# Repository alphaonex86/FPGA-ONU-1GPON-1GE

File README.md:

# FPGA-ONU

An open PON endpoint in one chip: 1 GPON/EPON ONU port (BOSA, to the ISP OLT), 1 SFP
cage (switch SFP, or EPON/GPON OLT module for the OLT role) and 1 Gigabit
Ethernet port, with the MACs, the Ethernet PHY and a RISC-V CPU integrated.
Developed and proven on an FPGA, the final target is an ASIC that holds everything.

## Goals

- GPON ONU MAC: GTC framing, FEC, AES-128 decryption, PLOAM, OMCI, upstream
  burst mode with DBA. EPON MAC (MPCP, OAM) and the OLT role of both.
- 1000BASE-T Ethernet port, PHY integrated in the target ASIC (FPGA phase: a
  copper SFP in an SFP+ cage on our HSMC card for the DE25-Standard; its other
  cage takes an OLT module or a normal SFP).
- SFP cage autodetects the module (EEPROM): 1000BASE-X, EPON OLT or GPON OLT.
- BOSA on board; all optics control (burst, APC, LOS, DDM) in the FPGA/ASIC
  logic; outside only analog: discrete RF transistors, a small ADC/DAC, the APD
  bias boost and passives (FPGA phase: an SY88236L BOSA driver on our HSMC
  card, straight to the DE25-Standard GTS transceivers).
- 32-bit RISC-V CPU (VexiiRiscv, rv32imac, no SIMD, no FPU), high energy
  efficiency, power management (clock gating, sleep states, DVFS); MMU (Sv32)
  so it runs Linux.
- Hardware acceleration (line rate, CPU off the data path): GPON, switching,
  VLAN, PPPoE, IPv4 and IPv6 routing, NAT.
- OpenWrt support: upstream-able riscv32 target, drivers for the GPON MAC and GE port.
- Firmware in an external, socketed, user-programmable flash.
- Behaves on the wire exactly like the stock ONU of each brand the OLT expects
  (ZTE, Huawei, ...): no unknown or unanswered message, no drop out of O5; the
  OLT side likewise mimics the stock OLT.
- ONU and OLT at once, each independent on its own segment; through software,
  the exchanges can be dumped and cloned into per-vendor profiles for everyone.
- Vendor-neutral RTL: vendor primitives only in thin wrappers, so the same tree
  goes from FPGA to ASIC.

## Layout

- `common/`: board-neutral parts: RTL and tests (`hw/`), KiCad generator and
  shared parts library (`pcb/gen`, `pcb/lib`).
- `agilex5/`: common to the Agilex 5 boards (Quartus benches, GTS lane variants).
- `de25-standard/`: Terasic DE25-Standard, our HSMC card (`pcb/hsmc`: two SFP+
  cages and the ONU BOSA; placed and routed, DRC/ERC clean, not yet ordered).
- `de25-nano/`: Terasic DE25-Nano, ECP5 SerDes bridge boards (alternative).

## Status

GPON OLT MAC in simulation (SpinalHDL): GTC downstream framer and deframer,
upstream burst receiver, ONU activation (serial number, ONU-ID, ranging, EqD)
with status-reporting DBA (DBRu), checked against G.984.3 vectors and Scala ONU models; the
OLT MAC top (311.04 / 155.52 MHz domains, CPU registers over APB with a
generated C header) meets timing on the DE25-Standard FPGA.
GPON ONU MAC in simulation: activation (O1-O7, TO1/TO2) with the fixed PLOAM set
in hardware (Acknowledge, Password, Alloc-ID and OMCI Port-ID), every other
PLOAM to the CPU, upstream burst framer timed to the bit from the downstream
frame (35 us response); checked in closed loop against our OLT MAC over a
simulated fibre (ranging, DBA, fibre cut and POPUP, Disable_Serial_Number),
and against the PLOAM sequences of real OLTs (ZTE as recorded by stock ONUs,
Broadcom Maple): every copy answered like the stock ONU, EqD drift updates to
the bit, deactivation churn; meets timing on the DE25-Standard FPGA. Like those
OLTs, our OLT sends each of its PLOAMs 3 times. OMCI over GEM both ways:
downstream fragments of the OMCI Port-ID to the CPU, CPU packets upstream in
the default allocation (OMCC), fragmented to the grant, and data GEM at the
same time in up to 4 data T-CONTs, each stream continuing its packet in its
next allocation. DBRu reports of the real backlog (reporting blocks rounded up,
G.984.3 Table 8-1 code, mode 0 and 1). Downstream AES-128
counter-mode decryption of the encrypted Port-IDs with the key switch at the
OLT's superframe, and downstream FEC: RS(255,239) decoding, up to 8 byte errors
corrected per codeword, with the counters of the OMCI FEC PM; checked against
the G.984.3 golden vectors (A.2.2, A.2.3 with FEC, A.3). The OLT sends
downstream FEC when enabled (CTRL register), every codeword's parity checked
against the model and decoded by our ONU in the closed loop. Upstream FEC in
the ONU when the OLT asks for it (Use_FEC): parity per codeword with the shorter
last one, the content sized to the data bytes, checked by a Scala OLT model; our
OLT does not ask for it (like Maple's default).
Ethernet port in simulation: comma alignment and 8b/10b on the raw 10-bit lane,
taxi's 1000BASE-X/SGMII PCS (autonegotiation) and 1G MAC (`common/hw/ext/taxi`,
submodule: `git submodule update --init`), two ports back to back; on the board
its own lane, SFP cage pins and HPS frame queues (`eth_board_regs.h`), checked
from the CPU registers to the looped-back lane.
L2 bridge GEM <-> Ethernet (`common/hw/spinal/pon/GemEthBridge.scala`,
`bridge_regs.h`): per Port-ID action towards Ethernet (drop, CPU, Ethernet;
whole frames with a good FCS), the outer VLAN ID or the untagged default picks
the Port-ID towards the PON, directly or by PCP (802.1p mapper), and the
Port-ID its T-CONT queue (4 on the ONU, each dropping when full without
blocking the others); VLAN treatments each way (G.988 ME 171 subset: push,
pop, translate, PCP set or kept; `VlanRewrite.scala`), the FCS computed after
the rewrite; store-and-forward queues across the four clocks, drops counted.
Flow offload in the bridge, each way (`FlowClassifier.scala`, mtk_ppe model):
frame parser (0-2 VLAN tags, PPPoE session, IPv4/IPv6 TCP/UDP), flow caches
keyed by the 5-tuple, outer VID and PPPoE session (2-way hash in block RAM,
written by the CPU, a hit bit per flow for the driver's stats: IPv4 2K flows
(1K on the board), IPv6 512, routed only, per direction), 64 egress entries (next hop and own MAC, PPPoE
session, VLAN treatment, Port-ID and queue); a hit is rewritten on its way out
(`FlowRewrite.scala`: MACs, PPPoE add/strip, NAPT, TTL or hop limit,
incremental IP and TCP/UDP checksums), a miss follows the L2 rules or, in flows mode (router: per
Port-ID or VLAN entry), goes to the CPU; on each board side the bridge's LAN and
WAN frame queues carry the misses to the CPU and the CPU's own frames out; control frames (ARP, PPPoE
discovery and LCP, DHCP, ICMPv6, IGMP, EAPOL, LLDP, slow protocols) get their own queues and interrupts
behind a token bucket per side, so a miss flood cannot delay them. On the board the Ethernet port goes to the CPU queues or to the
OLT or the ONU bridge (`eth_board_regs.h` BRIDGE); a frame from the lane reaches
the OLT MAC's downstream GEM, or the ONU MAC's upstream data stream, in
simulation; in the closed OLT <-> ONU loop, Ethernet frames cross both bridges
end to end each way, upstream in two T-CONTs granted by our OLT's DBA.
EPON MAC in simulation (`common/hw/spinal/pon/epon/`): clause 36 PCS (8b/10b,
comma sync at any bit slip) with the clause 65 LLID preamble and its CRC-8;
ONU MPCP (discovery with a random offset in the window, REGISTER_REQ/ACK,
timestamp sync and drift, GATE grants timed to the TQ with laser on/off and
sync time, REPORT, deregistration) and OLT MPCP (discovery windows, LLID
allocation, RTT per ONU, IPACT grants from the REPORTs within min/max, CPU and
timeout deregistration, the optics' receiver reset before each burst), checked
together over a simulated splitter with two
ONUs at different distances: no upstream collision, data per LLID each way.
Both MAC tops (`EponOnu.scala`, `EponOlt.scala`) run from their CPU registers
(`epon_onu_regs.h`, `epon_olt_regs.h`: configuration, registration state and
LLID, OLT events, frame counters, interrupts), checked through them alone;
on the DE25-Standard FPGA at 125 MHz: ONU 1.3K ALMs (211 MHz), OLT 2.5K ALMs
(141 MHz). With the same Ethernet bridges as GPON (`EponGem.scala`: the LLID is
the Port-ID, Port-ID 0xFFF the broadcast LLID; the ONU's REPORT from its queues),
Ethernet frames cross OLT port -> ONU port and back in simulation.
HSMC card GTS lanes (two SFP cages, ONU, burst enable) fit in Quartus at their
line rates from their refclk pins (`agilex5/gts/fit.sh`). One GTS dynamic
reconfiguration controller switches cage 0 and the ONU each on its own at run time
between GPON and 1.25 Gb/s, each profile on its own refclk: the cage 0 lane (GPON
OLT, or EPON OLT, 1000BASE-X or SGMII module) and the ONU BOSA lane with its
burst enable lane (EPON ONU); four combinations (GPON or 1.25 Gb/s per side), so
switching one side leaves the other running (to check on the board). Cage 0 with a normal SFP: the OLT core's own
Ethernet port replaces the EPON OLT MAC on the 1.25 Gb/s profile (`olt_board_regs.h`
ETH, set while the lane is reset; frames to the CPU queues at 0xA00), checked in
simulation through the lane; software picks the mode from the module's EEPROM.
Cage 1 is the Ethernet port's. In the board top the EPON MACs run on those profiles with the same bridges
and CPU queues, their registers on each side's bridge slave (0x800, the DR
controller's at 0x900 on the OLT's); the OLT's received words cross from each
profile's rx clock; the EPON ONU is loop-timed like the GPON one, by its own
VCXO loop on the 156.25 MHz VCXO; checked in simulation in both profiles.
Board top (`agilex5/hw/spinal/pon/PonBoard.scala`), OLT side: OLT MAC on its GTS lane
(2x oversampled upstream), HPS lightweight bridge to the MAC and board registers
(GTS reset/status, SFP cage pins, module I2C; `olt_board_regs.h`, `onu_board_regs.h`) and GEM CPU
queues for OMCI (whole packets downstream, upstream fragments with descriptors;
`gem_queues.h`). ONU side: ONU MAC on the BOSA data and burst enable lanes, its
clock kept on the recovered downstream clock by a VCXO loop (DDMTD phase
detector on a helper PLL, 6.7 ps steps, PI, sigma-delta: 0.03 bit of upstream
phase wander in simulation, the OLT tolerating 4), GEM CPU queues for OMCI,
optics pins with the laser held off until both lanes are up. Sniffer (ONU side, 0x900,
`sniffer_regs.h`; with a passive tap on a stock ONU's fibre, the BOSA receiving the downstream copy and a GPON
OLT module in cage 0 that ONU's bursts): one ONU's PLOAMs, BWmap
entries and GEM fragments (still ciphered) and its descrambled bursts, timestamped, read by the CPU as records;
the laser and cage 0's transmitter are held off while it records, and the module gets its burst reset before each
burst, planned from the captured BWmap; checked in simulation. HPS tool `common/sw/sniffer` (`make test`, `make
CC=aarch64-linux-gnu-gcc`): configures it from the exchange (ONU-ID, Alloc-IDs, OMCI Port-ID, delimiter), learns the
burst reset offset, writes raw records (`-w`, keep dumps out of this repo) and a decoded log, replays a dump (`-r`), waits on its interrupt
through UIO (`-u`, overlay from `de25-standard/ghrd/uio_overlay.sh`) or polls `/dev/mem`;
each burst is split by its matched grants into PLOAMu, DBRu and GEM frames, so the stock ONU's OMCI answers sit next
to the OLT's requests; `-P` writes them as an OMCI profile (whole messages paired by TCI: request, answer).
`common/sw/omci` (portable C, `make test`) loads such a profile and answers a request from it with the request's
TCI and a new trailer (AAL5 CRC-32): the clone path for MEs our ONU lacks.
`common/sw/linux` (GPL): the HPS driver of our ONU on the OpenWrt fork's GPON core (`make KDIR=...`): activation
stays in the FPGA, the core's OMCI responder answers on the OMCI Port-ID through the CPU GEM queues, and the core's
clone fallback answers what its ME model lacks from the binary profile (`common/sw/omci/omci_profile`). Not yet:
the Encryption_Key exchange, OMCI to bridge mapping.
Both sides checked in simulation, fit together on the DE25-Standard with the
HSMC card pins placed, flow engine, EPON OLT and ONU, cage 0's Ethernet port and the sniffer included: 40.5K ALMs (87 %), 308 of 358 M20K, setup slack +0.034 ns
(`agilex5/gts/fit.sh out/pon_board PonBoard`).
With the HPS: `de25-standard/ghrd/` brings Terasic's DE25-Standard reference design (GHRD, not in this
repository: `GHRD=<its folder> agilex5/gts/fit.sh <folder outside the repository> ghrd`) to Quartus 26.1, removes
its JTAG debug masters and shrinks its on-chip RAM to make room, and wires PonBoard in: its three register
windows on the HPS lightweight bridge (+0x100000 OLT, +0x101000 ONU, +0x102000 Ethernet), its 18 interrupts on
f2h_irq1 bits 0-17, its management clock the GHRD's 100 MHz: 42.7K ALMs (91 %), 312 of 358 M20K,
setup slack +0.017 ns. A fit folder holding an earlier fit made Quartus 26.1.1 crash (internal error 22912) or fail where a fresh
one passed, so fit.sh empties its own folder and refuses any other non-empty one. The HPS DDR settings were upgraded by Quartus: to check on the board.

## License

Hardware and RTL are licensed under the CERN Open Hardware Licence v2 -
Strongly Reciprocal ([CERN-OHL-S-2.0](LICENSE)). Exception: `common/sw/linux` (the Linux driver, built with the GPL GPON
core of the OpenWrt fork) is GPL-2.0-or-later.

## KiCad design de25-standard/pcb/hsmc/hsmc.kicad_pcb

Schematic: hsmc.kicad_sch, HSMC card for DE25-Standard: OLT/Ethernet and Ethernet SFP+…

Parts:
C1, C2, C7, C8, C11, C12, C15, C16, C18, C25, C27, C30, C32, C35, C36, C37, C38, C39, C40, C41, C42, C45, C46, C47, C48, C49, C51, C60, C61, C63, C65, C66: 100n; C_0402_1005Metric
C3, C4, C17, C26, C28, C31, C33, C43, C44, C50, C52: 10u; C_0603_1608Metric
C5, C6, C22, C23, C24, C29, C34: 22u; C_0805_2012Metric
C9, C10, C13, C14: 1u; C_0402_1005Metric
C19, C20: 10u; C_0805_2012Metric; MPN 10 uF 25 V X5R 0805
C21: 100n; C_0603_1608Metric; MPN 100 nF 25 V
C53, C54: 100n; C_0603_1608Metric; MPN 100 V X7R
C55: 220p; C_0603_1608Metric; MPN 100 V X7R
C56: 47n; C_0402_1005Metric
C57: 2.2u; C_0603_1608Metric
C58, C59: 10p; C_0402_1005Metric
C62: 100n; C_0603_1608Metric; MPN 100 nF 50 V X7R 0603
C64: 47p; C_0402_1005Metric
D1: BAT46WJ; D_SOD-323F; MPN BAT46WJ (100 V)
FB1, FB2, FB3, FB4: 120R@100MHz; L_0603_1608Metric; MPN BLM18PG121SN1D
H1, H2: M3; MountingHole_3.2mm_M3
J1: ASP-122952-01; HSMC_ASP-122952-01; MPN Samtec ASP-122952-01
J2: SFP0 cage; Connector_SFP_and_Cage; MPN SFP+ cage (SFF-8432) + 20-pin host conn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
J3: SFP1 cage; Connector_SFP_and_Cage; MPN SFP+ cage (SFF-8432) + 20-pin host conn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
L1: 2.2u; L_Cenker_CKCS4020; MPN 2.2 uH, Isat >= 4 A, 4020
L2, L3, L4, L5: 1u; L_0805_2012Metric; MPN 1 uH >= 1 A, low DCR
L6: 4.7u; L_Cenker_CKCS252012; MPN 4.7 uH, Isat >= 1 A, 2520
R1, R2, R5, R6: 150; R_0402_1005Metric
R3, R4, R7, R8, R10, R32, R34, R45, R51: 10k; R_0402_1005Metric
R9: 33.2k; R_0402_1005Metric
R11, R19: 33; R_0402_1005Metric
R12, R20: 330; R_0402_1005Metric
R13, R14, R15, R16, R17, R18, R21, R22, R23, R24, R25, R26, R27, R28, R52, R53, R57: 4.7k; R_0402_1005Metric
R29: 5.1k; R_0402_1005Metric
R30: 6.2k; R_0402_1005Metric
R31, R46: 20k; R_0402_1005Metric
R33: 12k; R_0402_1005Metric
R35: 5.6k; R_0402_1005Metric
R36: 3.9k; R_0402_1005Metric
R37, R49: 1.5k; R_0402_1005Metric
R38, R43, R56: 1k; R_0402_1005Metric
R39, R41, R48: 10; R_0402_1005Metric
R40: 15; R_0402_1005Metric
R42: 100; R_0402_1005Metric
R44: 300k; R_0603_1608Metric
R47: 33k; R_0402_1005Metric
R50: 3.01k; R_0402_1005Metric
R54: 0; R_0402_1005Metric; not fitted
R55: 15k; R_0402_1005Metric
R58, R59, R60, R61: 20; R_0402_1005Metric
U1: TPS563201DDCR; SOT-23-6; MPN TPS563201DDCR
U2: SY88236LMG; QFN-32-1EP_5x5mm_P0.5mm_EP3.1x3.1mm_ThermalVias; MPN SY88236LMG
U3: SN65LVDT2DBVR; SOT-23-5; MPN SN65LVDT2DBVR
U4: BOSA GPON (X100DG); BOSA_GPON; MPN desoldered from an X100DG; pad order to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
U5: TPS61391RTER; WQFN-16-1EP_3x3mm_P0.5mm_EP1.68x1.68mm_ThermalVias; MPN TPS61391RTER
U6: AD5593RBRUZ; TSSOP-16_4.4x5mm_P0.65mm; MPN AD5593RBRUZ
U7: SN74LVC1G123DCUR; VSSOP-8_2.3x2mm_P0.5mm; MPN SN74LVC1G123DCUR
U8: SN74LVC1G97DBVR; SOT-23-6; MPN SN74LVC1G97DBVR
U9: SN74LVC1G32DBVR; SOT-23-5; MPN SN74LVC1G32DBVR
Y1: SiT3821 156.25 MHz; Oscillator_SMD_SiTime_SiT9121-6Pin_3.2x2.5mm; MPN SiT3821AI-1B2-33NH156.250000
Y2: SiT3821 155.52 MHz; Oscillator_SMD_SiTime_SiT9121-6Pin_3.2x2.5mm; MPN SiT3821AI-1B2-33NE155.520000

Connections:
+3V3: C1.1, C2.1, C3.1, C4.1, C5.1, C6.1, C61.1, C63.1, C65.1, C66.1, FB1.1, FB2.1, FB4.1, J1.45 (3.3V), J1.51 (3.3V), J1.57 (3.3V), J1.63 (3.3V), J1.69 (3.3V), J1.75 (3.3V), J1.81 (3.3V), J1.87 (3.3V), J1.93 (3.3V), J1.99 (3.3V), J1.105 (3.3V), J1.111 (3.3V), J1.117 (3.3V), J1.123 (3.3V), J1.129 (3.3V), J1.135 (3.3V), J1.141 (3.3V), J1.147 (3.3V), J1.153 (3.3V), J1.159 (3.3V), R27.2, R28.2, R51.2, R52.2, R53.2, R55.2, R57.2, U6.3 (V_{DD}), U6.9 (V_{LOGIC}), U7.3 (~CLR), U7.8 (VCC), U8.5 (VCC), U9.5 (VCC)
+3V3_APD: C51.1, C52.1, FB4.2, L6.1, R48.1, U5.10 (VIN), U5.13 (EN)
+3V3_APDA: C57.1, R48.2, U5.14 (AVCC), U5.15 (AVCC)
+3V3_OPT: C39.1, C40.1, C41.1, C42.1, C43.1, C44.1, C45.1, FB2.2, FB3.1, R29.2, R40.2, U2.17 (VCC), U2.20 (VCC), U2.32 (VCC), U3.1 (VCC), U4.T1 (LD_A), U4.T4 (MPD_K)
+3V3_RX: C48.1, C49.1, C50.1, FB3.2, U4.R2 (VCC)
+3V3_SFP: C22.1, C23.1, C24.1, C29.1, C34.1, L1.2, L2.1, L3.1, L4.1, L5.1, R9.1, R13.2, R14.2, R15.2, R16.2, R17.2, R18.2, R21.2, R22.2, R23.2, R24.2, R25.2, R26.2
+3V3_SFP0R: C27.1, C28.1, J2.15 (VccR), L3.2
+3V3_SFP0T: C25.1, C26.1, J2.16 (VccT), L2.2
+3V3_SFP1R: C32.1, C33.1, J3.15 (VccR), L5.2
+3V3_SFP1T: C30.1, C31.1, J3.16 (VccT), L4.2
+3V3_XO: C15.1, C16.1, C17.1, FB1.2, Y1.6 (VDD), Y2.6 (VDD)
+12V: C19.1, C20.1, C21.1, J1.88 (12V), J1.94 (12V), J1.100 (12V), U1.3 (VIN), U1.5 (EN)
APCFAULT_N: U2.25 (~APCFAULT), U6.13 (IO7)
APCSET: R31.1, R32.1, U2.12 (APCSET)
APC_ADJ: R32.2, U6.4 (IO0)
APD_ADJ: R46.2, U6.6 (IO2)
APD_CAP: C56.1, U5.9 (CAP)
APD_FB: R44.2, R45.1, R46.1, U5.12 (FB)
APD_ISHORT: R47.1, U5.11 (ISHORT)
APD_MON: C58.1, R49.1, U5.4 (MON1), U6.11 (IO5)
APD_MON2: C59.1, R50.1, U5.3 (MON2)
BEN_DLY: C64.1, R56.2, U8.1 (IN1)
BEN_IO: J1.120 (LVDS_RXp11), R54.1
BIASMAX: R35.1, U2.14 (BIASMAX)
BIASMON: R37.1, U2.23 (BIASMON), U6.7 (IO3)
BST_SFP: C18.1, U1.6 (VBST)
BURST_CUT: J1.116 (LVDS_RXn10), U8.4 (Y), U9.2
CUT_C: C62.1, U7.6 (Cext)
CUT_Q: U7.5 (Q), U8.6 (IN2)
CUT_RC: C62.2, R55.1, U7.7 (RCext)
DDM_RESET: R51.1, U6.1 (~RESET)
DDM_VREF: C60.1, U6.8 (V_{REF})
FB_SFP: R9.2, R10.1, U1.4 (VFB)
GND: C1.2, C2.2, C3.2, C4.2, C5.2, C6.2, C9.2, C10.2, C13.2, C14.2, C15.2, C16.2, C17.2, C19.2, C20.2, C21.2, C22.2, C23.2, C24.2, C25.2, C26.2, C27.2, C28.2, C29.2, C30.2, C31.2, C32.2, C33.2, C34.2, C39.2, C40.2, C41.2, C42.2, C43.2, C44.2, C45.2, C48.2, C49.2, C50.2, C51.2, C52.2, C53.2, C54.2, C55.2, C56.2, C57.2, C58.2, C59.2, C60.2, C61.2, C63.2, C64.2, C65.2, C66.2, J1.160 (PSNTn), J1.161 (GND), J1.162 (GND), J1.163 (GND), J1.164 (GND), J1.165 (GND), J1.166 (GND), J1.167 (GND), J1.168 (GND), J1.169 (GND), J1.170 (GND), J1.171 (GND), J1.172 (GND), J2.1 (VeeT), J2.10 (VeeR), J2.11 (VeeR), J2.14 (VeeR), J2.17 (VeeT), J2.20 (VeeT), J2.CAGE, J3.1 (VeeT), J3.10 (VeeR), J3.11 (VeeR), J3.14 (VeeR), J3.17 (VeeT), J3.20 (VeeT), J3.CAGE, R1.2, R2.2, R5.2, R6.2, R10.2, R30.2, R31.2, R33.2, R35.2, R36.2, R37.2, R38.2, R45.2, R47.2, R49.2, R50.2, U1.1 (GND), U2.1 (LOS/SD_SEL), U2.5 (GND), U2.8 (GND), U2.16 (GND), U2.24 (GND), U2.29 (GND), U2.33 (EP), U3.2 (GND), U4.R5 (GND), U5.7 (GND), U5.16 (AGND), U5.17 (EP), U6.2 (A0), U6.14 (GND), U7.1 (~A), U7.4 (GND), U8.2 (GND), U8.3 (IN0), U9.3 (GND)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
GTS_REFCLK_AC_N: C8.2, R59.1
GTS_REFCLK_AC_P: C7.2, R58.1
GTS_REFCLK_N: J1.8 (XCVR_RXn6), R59.2
GTS_REFCLK_P: J1.6 (XCVR_RXp6), R58.2
GTS_RXREF_AC_N: C12.2, R61.1
GTS_RXREF_AC_P: C11.2, R60.1
GTS_RXREF_N: J1.4 (XCVR_RXn7), R61.2
GTS_RXREF_P: J1.2 (XCVR_RXp7), R60.2
HV_APD: C55.1, U4.R1 (VAPD), U5.5 (APD)
HV_FILT: C54.1, R42.2, R43.1
HV_MONIN: R43.2, U5.6 (MONIN)
HV_OUT: C53.1, D1.1 (K), R42.1, R44.1
HV_SW: D1.2 (A), L6.2, U5.8 (SW)
LASER_DIS: R27.1, U2.11 (TXDIS), U9.4
LASER_DIS_FPGA: J1.102 (LVDS_RXp8), R57.1, U9.1
LD_BEN: R54.2, R56.1, U2.9 (BEN+), U3.5 (R), U7.2 (B)
LD_BEN_N: R30.1, U2.10 (BEN-)
LD_BIAS: R41.1, U2.21 (BIAS)
LD_K: R39.2, R41.2, U4.T2 (LD_K)
LD_MD: U2.22 (MD), U4.T3 (MPD_A)
LD_MODN: R40.1, U2.18 (MOD-)
LD_MODP: R39.1, U2.19 (MOD+)
LOSLVL: R29.1, U2.2 (LOSLVL)
MODMON: R36.1, U2.15 (MODMON), U6.10 (IO4)
MODSET: R33.1, R34.1, U2.13 (MODSET)
MOD_ADJ: R34.2, U6.5 (IO1)
ONU_BEN_N: J1.31 (XCVR_TXn0), U3.4 (B)
ONU_BEN_P: J1.29 (XCVR_TXp0), U3.3 (A)
ONU_RD_N: C38.1, U2.30 (ROUT-)
ONU_RD_P: C37.1, U2.31 (ROUT+)
ONU_RX_N: C38.2, J1.26 (XCVR_RXp1)
ONU_RX_P: C37.2, J1.28 (XCVR_RXn1)
ONU_SCL: J1.108 (LVDS_RXp9), R52.1, U6.16 (SCL)
ONU_SDA: J1.110 (LVDS_RXn9), R53.1, U6.15 (SDA)
ONU_TD_N: C36.2, U2.6 (DIN+)
ONU_TD_P: C35.2, U2.7 (DIN-)
ONU_TX_N: C36.1, J1.25 (XCVR_TXp1)
ONU_TX_P: C35.1, J1.27 (XCVR_TXn1)
RIN_N: C47.2, U2.28 (RIN-)
RIN_P: C46.2, U2.27 (RIN+)
RSSI: R38.1, U2.26 (RSSI), U6.12 (IO6)
RX_SD: J1.104 (LVDS_RXn8), R28.1, U2.3 (LOS/SD), U2.4 (~JAM)
SFP0_LOS: J1.48 (LVDS_RXp0), J2.8 (RX_LOS), R15.1
SFP0_MOD_ABS: J1.50 (LVDS_RXn0), J2.6 (MOD_ABS), R16.1
SFP0_P7: J2.7 (RS0), R11.2
SFP0_P9: J2.9 (RS1), R12.2
SFP0_RD_N: J1.18 (XCVR_RXp3), J2.12 (RD-)
SFP0_RD_P: J1.20 (XCVR_RXn3), J2.13 (RD+)
SFP0_RS0: J1.60 (LVDS_RXp2), R11.1
SFP0_RS1: J1.62 (LVDS_RXn2), R12.1
SFP0_SCL: J1.54 (LVDS_RXp1), J2.5 (SCL), R17.1
SFP0_SDA: J1.56 (LVDS_RXn1), J2.4 (SDA), R18.1
SFP0_TD_N: J1.19 (XCVR_TXn3), J2.19 (TD-)
SFP0_TD_P: J1.17 (XCVR_TXp3), J2.18 (TD+)
SFP0_TX_DIS: J1.42 (D1), J2.3 (TX_DISABLE), R14.1
SFP0_TX_FAULT: J1.44 (D3), J2.2 (TX_FAULT), R13.1
SFP1_LOS: J1.72 (LVDS_RXp4), J3.8 (RX_LOS), R23.1
SFP1_MOD_ABS: J1.74 (LVDS_RXn4), J3.6 (MOD_ABS), R24.1
SFP1_P7: J3.7 (RS0), R19.2
SFP1_P9: J3.9 (RS1), R20.2
SFP1_RD_N: J1.22 (XCVR_RXp2), J3.12 (RD-)
SFP1_RD_P: J1.24 (XCVR_RXn2), J3.13 (RD+)
SFP1_RS0: J1.84 (LVDS_RXp6), R19.1
SFP1_RS1: J1.86 (LVDS_RXn6), R20.1
SFP1_SCL: J1.78 (LVDS_RXp5), J3.5 (SCL), R25.1
SFP1_SDA: J1.80 (LVDS_RXn5), J3.4 (SDA), R26.1
SFP1_TD_N: J1.23 (XCVR_TXn2), J3.19 (TD-)
SFP1_TD_P: J1.21 (XCVR_TXp2), J3.18 (TD+)
SFP1_TX_DIS: J1.66 (LVDS_RXp3), J3.3 (TX_DISABLE), R22.1
SFP1_TX_FAULT: J1.68 (LVDS_RXn3), J3.2 (TX_FAULT), R21.1
SW_SFP: C18.2, L1.1, U1.2 (SW)
TIA_N: C47.1, U4.R4 (OUT-)
TIA_P: C46.1, U4.R3 (OUT+)
VCXO156_N: C8.1, R2.1, Y1.5 (OUT-)
VCXO156_P: C7.1, R1.1, Y1.4 (OUT+)
VCXO156_PWM: J1.122 (LVDS_RXn11), R3.1
VCXO156_RC: C9.1, R3.2, R4.1
VCXO156_VC: C10.1, R4.2, Y1.1 (VIN)
VCXO_N: C12.1, R6.1, Y2.5 (OUT-)
VCXO_P: C11.1, R5.1, Y2.4 (OUT+)
VCXO_PWM: J1.114 (LVDS_RXp10), R7.1
VCXO_RC: C13.1, R7.2, R8.1
VCXO_VC: C14.1, R8.2, Y2.1 (VIN)

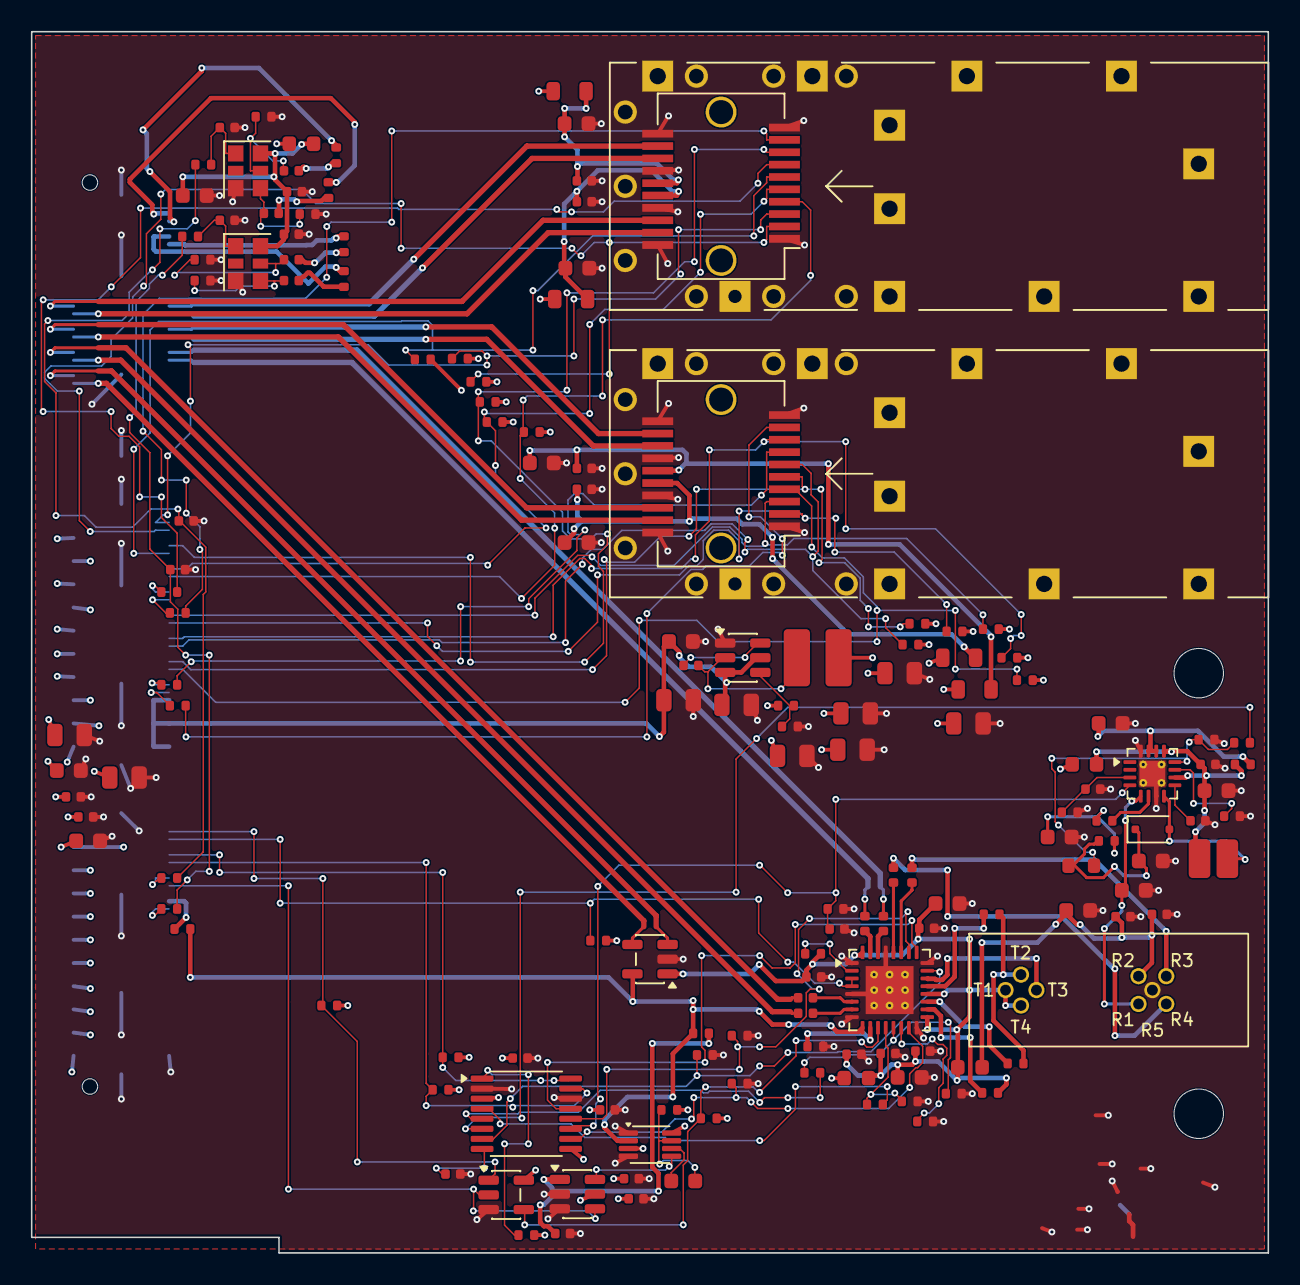
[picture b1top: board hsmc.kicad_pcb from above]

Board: 4 copper layers, 80.0 x 79.0 mm, 154 parts (1 on the bottom side), 117 nets.

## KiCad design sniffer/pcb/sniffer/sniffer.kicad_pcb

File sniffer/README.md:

# GPON sniffer

A passive tap on one ONU's drop fibre: both directions of that ONU's GPON traffic,
filtered to what concerns it, dumped with the direction of every record. Simple and
cheap: one small card on the DE25-Nano 40-pin GPIO. Origin: `../common/sniffer/sniffer-GPON.jpg`.

Versus the FPGA ONU (operator, 2026-11-02): the ONU + OLT proxy of this repo sits in the path
and can intervene in the packets; the sniffer cannot touch anything, it only listens, but it
dumps without complications (no activation, no cloning, the stock ONU keeps its link).

## Decisions (operator, 2026-11-02)

- Customer side, not provider: the OLT is the ISP's, remote and out of our hands. The tap goes
  between the wall fibre outlet and our own ONU; the sniffer must stay invisible to the ISP
  (passive, never emits; our ONU receives about 4 dB less, see Coupler).
- The link: about 5 km of fibre from the ISP; our ONU reports
  -17 to -27 dBm received. -27 dBm is already at a class B+ ONU's sensitivity (-27/-28 dBm),
  so any optical tap that takes light from the downstream can drop our ONU off the PON.
  Range across installations: the sniffer is for homes at -23 dBm or better (Coupler).
- Tap: two 1x2 couplers back to back in our ONU's drop (Coupler below), so the two
  directions arrive on two fibres (no WDM) and the upstream holds our ONU's bursts only,
  at one constant power.
- Optics: two BOSAs, receive only. Downstream: an ONU BOSA RX (X100DG, 1490 nm, APD-TIA).
  Upstream: the OLT BOSA XL-BCB2111-LS-02 RX (1310 nm, 1.25 Gb/s APD-TIA, -32 dBm). Each
  into a SY88349NDL limiting amp. No laser driver is fitted: the sniffer cannot emit into
  the PON, by construction. SFP modules were dropped: no raw GPON ONU module without a MAC
  on AliExpress (only "sticks" with a MAC); raw ones exist at Optcore/FiberMall/PLANET.
- Platform: an ECP5 SerDes card on the DE25-Nano GPIO (the `../de25-nano/pcb` bridge
  plan; the operator owns a DE25-Nano). The ECP5 deserialises; the Agilex runs the existing GTC deframer, FEC, AES
  and the filter; the HPS writes the dump.

## Coupler (operator, 2026-11-02)

Two 1x2 back to back: wall - [common 1x2 #1 50 %] - [90 % 1x2 #2 common] - ONU. The free leg of #1
is the downstream copy, the 10 % leg of #2 the upstream copy (one 1x2 alone taps one direction:
the light entering a leg leaves by the common port). #1 is a 50:50, #2 a 90:10: the
operator has several of each (unbalanced 1x2 for building GPON networks).
- ONU: about 4 dB less (3.5 + 0.5). The -17 to -27 dBm range is across installations, so the
  sniffer fits a home whose ONU reports -23 dBm or better without the tap (it then stays at
  -27 dBm or better, a class B+ ONU's sensitivity).
- Downstream: the sniffer gets the ONU's tapped level + 0.5 dB, at least -26.5 dBm there, above
  the APD's -28 dBm.
- Upstream: the ONU emits +0.5 to +5 dBm, the sniffer sees about -10 to -5.5 dBm, near an APD's
  overload (-8 dBm typical for an OLT receiver): a 5 dB SC attenuator on the upstream tap fibre.

## DE25-Nano: verified (2026-11-02)

- GPIO headers are 3.3 V HVIO: 100 MHz SDR or 200 Mb/s DDR per pin (Altera Agilex 5 GPIO
  architecture brief); the HVIO clock input reaches the I/O PLL up to 156.25 MHz (data sheet).
- So the card sends DDR: DS 2.48832 Gb/s on 16 pins + US 1.24416 Gb/s on 8 pins, 155.52 Mb/s
  per pin (78 % of the limit) on a 77.76 MHz forwarded clock. With CCLK/MOSI/MISO/SN/PROGRAMN
  (slave-SPI configuration from the Agilex) and I2C: 36 of the 40 pins of GPIO_0.
- The Agilex A5EB013 is the DE25-Standard's density (138K LE), where the GTC/FEC/AES already
  meet timing; the HPS has the GbE port and the microSD for the dump.
- The two ECP5 bridge boards in `../de25-nano/pcb` send 155.52 MHz SDR: above the 100 MHz HVIO limit.

## Card (`pcb/sniffer`, generated by `../common/pcb/gen`)

Routed 2026-11-02: KRT, then close_opens on the last 5 nets; KiCad: 0 errors, 0 unconnected.

ECP5 LFE5UM-25F (as the bridge boards), SerDes RX only: CH0 downstream (CDR), CH1 upstream
(lock-to-reference on the 155.52 MHz VCXO, which the ECP5 locks to the downstream like the
ONU board, so each burst needs only a phase pick). Each BOSA: receive can only, into a
SY88349NDL burst-mode limiting amp (SD mode, auto reset, squelch), its own TPS61391 APD bias
(DAC trim from an AD5593R, which also reads both APD currents = optical power at the tap).
Upstream coupling 220 pF (tau 11 ns), downstream 100 nF.

## Filter (downstream; the upstream is already this ONU only)

The ONU is named by its serial number. From the PLOAMs: Assign_ONU-ID (serial ->
ONU-ID), Assign_Alloc-ID, Configure_Port-ID (OMCI); from OMCI: the GEM Port CTPs
(data Port-IDs). Kept: PLOAMs to that ONU-ID or broadcast, the BWmap entries of its
Alloc-IDs, the GEM frames of its Port-IDs.

## RTL (`../common/hw/spinal/pon/sniffer`, test `pon.sniffer.SnifferTest`)

Vendor-neutral SpinalHDL, one line byte per clock per direction; no AES in hardware.
- `SnifferDs` (311.04 MHz): the GTC deframer (FEC included), then the filter: PLOAMs to
  `onuId` or broadcast (all with `allPloams`), BWmap entries and GEM fragments by two
  4096-bit maps (Alloc-ID, Port-ID) the HPS writes. GEM stays ciphered; its record carries
  the crypto-counter, the software decrypts.
- `SnifferUs` (155.52 MHz): delimiter hunt on any bit alignment, descramble from the BIP,
  one record per burst until 8 squelched (zero) line bytes.
- `RecordWriter`: the record stream; a record is kept or dropped whole, a full data FIFO
  cuts its tail (flag bit 7); drop and truncation counters.

Record: `0xA0|kind`, flags, payload length (16 LE), time (64 LE), payload.

| kind | payload | flags |
|------|---------|-------|
| 0 PLOAM | 12 bytes | 0: bad CRC |
| 1 allocation | 7 bytes as on the line | 0: bad CRC |
| 2 GEM fragment | Port-ID 16, PLI 16, counter 48, data | 2..0: PTI, 3: cut |
| 3 upstream burst | BIP, ONU-ID, Ind, allocations | 0: maxBytes reached |

ECP5 (`ecp5/`, `sh sniffer/ecp5/build.sh` -> `out/ecp5/sniffer.bit`, yosys + nextpnr + trellis):
`sniffer_ecp5.v` (DCU, resets, PLL, DDR pins) around `SnifferBridge` (test `pon.sniffer.SnifferBridgeTest`);
`gen.py` writes the DCU parameters and the LPF from the routed board. All in the VCXO's domain
(124.416 MHz, CH0's TX clock): CH1 is read there; the downstream crosses a 16-word FIFO whose
fill is the phase detector of the VCXO loop (PI every 132 us, sigma-delta on VCXO_PWM;
`ecp5/vcxo_loop_model.py`: locked to 0.5 word in 14 s from 10 ppm). Upstream: one sample per
pair, the centre of isolated 1- or 3-sample runs (an edge on a sample reads either bit).
Timing (speed 6): VCXO domain 135.6 MHz for 124.4, out 125 for 77.8, DS 255 for 124.4.

Still to write: the Agilex wrapper (DDR capture, x4 / x2 serialisers, time base, both
streams to the HPS).

## Dump

pcapng, one interface per direction (0 = downstream, 1 = upstream), hardware
timestamps; one packet per record.

## Open

- SY88349NDL stock (LCSC not reachable from here) and its SD level resistor (5.1k start).
- Lead order of the X100DG BOSA's RX can (to measure); XL-BCB2111 order from its drawing.
- XL-BCB2111 connector: SC/UPC in the title, SC/APC on the drawing.
- CH1 between bursts: with the line squelched the DCU sees LOS and its phase detector stops
  (`PDEN_SEL`); the 2x pick needs the DCO to stay on the reference frequency there, to measure.
- DCU bit order: the first received bit taken in D0 (as LiteICLink's 8b10b path); a reversed
  lane would show as a deframer that never syncs.
- VCXO: its pull range must exceed its initial error plus ageing (SiT3821: pick >= +-100 ppm).
- ECP5 in the BOM is the C grade (LFE5UM-25F-6BG381C): the I grade is the industrial one.
- 5 dB attenuator part number; connectors (drop SC/APC, BOSA pigtails per part).

## Docs

`../common/sniffer/`: block diagram (`sniffer-diagram.dot` -> `.svg`/`.png`) and the prompt for a
realistic photo of the finished device (`sniffer-render-prompt.md`, Nano Banana Pro).

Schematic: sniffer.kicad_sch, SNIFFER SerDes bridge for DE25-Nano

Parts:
C1, C3, C6, C9, C24, C25, C30, C48, C49, C50, C51, C54, C57, C60, C63, C65, C71, C80, C87, C96: 10u; C_0603_1608Metric
C2, C4, C5, C7, C8, C10, C11: 22u; C_0805_2012Metric
C12, C13, C66, C67: 1u; C_0402_1005Metric
C14, C15, C16, C17, C18, C19, C20, C21, C22, C23, C26, C27, C28, C29, C31, C32, C33, C34, C35, C36, C37, C38, C39, C40, C41, C42, C43, C44, C45, C46, C47, C52, C53, C55, C56, C58, C59, C61, C62, C64, C68, C69, C70, C72, C73, C74, C75, C76, C77, C78, C79, C83, C84, C85, C86, C95, C104, C105: 100n; C_0402_1005Metric
C81, C82: 220p; C_0402_1005Metric
C88, C89, C97, C98: 100n; C_0603_1608Metric; MPN 100 V X7R
C90, C99: 220p; C_0603_1608Metric; MPN 100 V X7R
C91, C100: 47n; C_0402_1005Metric
C92, C101: 2.2u; C_0603_1608Metric
C93, C94, C102, C103: 10p; C_0402_1005Metric
D1, D2: BAT46WJ; D_SOD-323F; MPN BAT46WJ (100 V)
FB1, FB2, FB3, FB4, FB5, FB6, FB7, FB8, FB9, FB10: 120R@100MHz; L_0603_1608Metric; MPN BLM18PG121SN1D
H1, H2: M3; MountingHole_3.2mm_M3
J1: DE25-Nano GPIO; PinSocket_2x20_P2.54mm_Vertical
J2: JTAG; PinHeader_1x06_P2.54mm_Vertical
L1, L2: 2.2u; L_Cenker_CKCS252012; MPN CKCS252012-2R2M
L3, L4: 4.7u; L_Cenker_CKCS252012; MPN 4.7 uH, Isat >= 1 A, 2520
R1, R3: 100k; R_0402_1005Metric
R2, R4: 120k; R_0402_1005Metric
R5, R6, R7, R8, R9, R12, R13, R14, R20, R24: 4.7k; R_0402_1005Metric
R10, R15, R16, R28, R37, R43, R46: 10k; R_0402_1005Metric
R11, R26, R35: 1k; R_0402_1005Metric
R17, R18, R21, R22: 49.9; R_0402_1005Metric
R19, R23: 5.1k; R_0402_1005Metric
R25, R34: 100; R_0402_1005Metric
R27: 300k; R_0603_1608Metric
R29, R38: 20k; R_0402_1005Metric
R30, R39: 33k; R_0402_1005Metric
R31, R40: 10; R_0402_1005Metric
R32, R41: 1.5k; R_0402_1005Metric
R33, R42: 3.01k; R_0402_1005Metric
R36: 330k; R_0603_1608Metric
R44, R45: 2.2k; R_0402_1005Metric
RN1, RN2, RN3, RN4, RN5, RN6, RN7: 22; R_Array_Convex_4x0402; MPN 4D02WGJ0220TCE
U1, U2: TLV62569DBVR; SOT-23-5; MPN TLV62569DBVR
U3: TLV75525PDBVR; SOT-23-5; MPN TLV75525PDBVR
U4: LFE5UM-25F-6BG381C; Lattice_caBGA-381_17x17mm_Layout20x20_P0.8mm; MPN LFE5UM-25F-6BG381C
U5: BOSA GPON (X100DG), RX can only; BOSA_GPON
U6, U8: SY88349NDLMG; QFN-16-1EP_3x3mm_P0.5mm_EP1.7x1.7mm_ThermalVias; MPN SY88349NDLMG
U7: XL-BCB2111-LS-02, RX can only; BOSA_RX_TO46
U9, U10: TPS61391RTER; WQFN-16-1EP_3x3mm_P0.5mm_EP1.68x1.68mm_ThermalVias; MPN TPS61391RTER
U11: AD5593RBRUZ; TSSOP-16_4.4x5mm_P0.65mm; MPN AD5593RBRUZ
Y1: SiT3821 155.52 MHz; Oscillator_SMD_SiTime_SiT9121-6Pin_3.2x2.5mm; MPN SiT3821AI-2B2-33NB155.520000 (LVDS, +-5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

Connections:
+1V1: C7.1, C8.1, C14.1, C15.1, C16.1, C17.1, C18.1, C19.1, C20.1, C21.1, C22.1, C23.1, C24.1, C25.1, L1.2, R1.1, U4.H8 (VCC), U4.H9 (VCC), U4.H10 (VCC), U4.H11 (VCC), U4.H12 (VCC), U4.H13 (VCC), U4.J8 (VCC), U4.J13 (VCC), U4.K8 (VCC), U4.K13 (VCC), U4.L8 (VCC), U4.L13 (VCC), U4.M8 (VCC), U4.M13 (VCC), U4.N8 (VCC), U4.N9 (VCC), U4.N10 (VCC), U4.N11 (VCC), U4.N12 (VCC), U4.N13 (VCC)
+1V1_HRX: C58.1, C59.1, C60.1, FB4.2, U4.T8 (VCCHRX0_D0CH0), U4.T9 (VCCHRX1_D0CH1)
+1V1_HTX: C55.1, C56.1, C57.1, FB3.2, U4.T7 (VCCHTX0_D0CH0), U4.T10 (VCCHTX1_D0CH1)
+1V1_SD: C10.1, C11.1, FB2.1, FB3.1, FB4.1, L2.2, R3.1
+1V1_VCCA: C52.1, C53.1, C54.1, FB2.2, U4.T6 (VCCA0), U4.U6 (VCCA0)
+2V5: C13.1, FB1.1, FB5.1, U3.5 (OUT)
+2V5_AUX: C26.1, C27.1, C28.1, C29.1, C30.1, FB1.2, U4.F6 (VCCAUX), U4.F15 (VCCAUX), U4.P6 (VCCAUX), U4.P15 (VCCAUX)
+2V5_AUXA: C61.1, C62.1, C63.1, FB5.2, U4.V10 (VCCAUXA0), U4.V11 (VCCAUXA0)
+3V3: C3.1, C4.1, C5.1, C12.1, C31.1, C32.1, C33.1, C34.1, C35.1, C36.1, C37.1, C38.1, C39.1, C40.1, C41.1, C42.1, C43.1, C44.1, C45.1, C46.1, C47.1, C48.1, C49.1, C50.1, C51.1, C105.1, FB6.1, FB7.1, FB8.1, FB9.1, FB10.1, J1.29, J2.1, R5.2, R6.2, R7.2, R8.2, R9.2, R10.2, R11.2, R12.2, R13.2, R20.2, R24.2, R43.2, R44.2, R45.2, R46.2, U3.1 (IN), U3.3 (EN), U4.F9 (VCCIO0), U4.F10 (VCCIO0), U4.F11 (VCCIO1), U4.F12 (VCCIO1), U4.H6 (VCCIO7), U4.H7 (VCCIO7), U4.H14 (VCCIO2), U4.H15 (VCCIO2), U4.J6 (VCCIO7), U4.J15 (VCCIO2), U4.L6 (VCCIO6), U4.L7 (VCCIO6), U4.L14 (VCCIO3), U4.L15 (VCCIO3), U4.M6 (VCCIO6), U4.M15 (VCCIO3), U4.P9 (VCCIO8), U4.P10 (VCCIO8), U11.3 (V_{DD}), U11.9 (V_{LOGIC})
+3V3_DS_APD: C86.1, C87.1, FB9.2, L3.1, R31.1, U9.10 (VIN), U9.13 (EN)
+3V3_DS_APDA: C92.1, R31.2, U9.14 (AVCC), U9.15 (AVCC)
+3V3_DS_OPT: C68.1, C69.1, C70.1, C71.1, FB7.2, R19.2, U5.R2 (VCC), U6.5 (VCC), U6.13 (LOS/SD_SEL), U6.16 (VCC)
+3V3_US_APD: C95.1, C96.1, FB10.2, L4.1, R40.1, U10.10 (VIN), U10.13 (EN)
+3V3_US_APDA: C101.1, R40.2, U10.14 (AVCC), U10.15 (AVCC)
+3V3_US_OPT: C77.1, C78.1, C79.1, C80.1, FB8.2, R23.2, U7.1 (VCC), U8.5 (VCC), U8.13 (LOS/SD_SEL), U8.16 (VCC)
+3V3_XO: C64.1, C65.1, FB6.2, Y1.6 (VDD)
+5V: C1.1, C2.1, C6.1, C9.1, J1.11, U1.1 (EN), U1.4 (VIN), U2.1 (EN), U2.4 (VIN)
CCLK: J1.15, R11.1, U4.U3 (CCLK)
CFG0: R5.1, U4.U4 (CFG_0)
DDM_RESET: R43.1, U11.1 (~RESET)
DDM_VREF: C104.1, U11.8 (V_{REF})
DONE: R8.1, U4.Y3 (DONE)
DS0: J1.13, RN4.5 (R4.2)
DS0_S: RN4.4 (R4.1), U4.B12 (PT35A/PCLKT1_0)
DS1: J1.14, RN4.6 (R3.2)
DS1_S: RN4.3 (R3.1), U4.B11 (PT29A/PCLKT0_0)
DS2: J1.16, RN4.7 (R2.2)
DS2_S: RN4.2 (R2.1), U4.A11 (PT27B/PCLKC0_1)
DS3: J1.18, RN4.8 (R1.2)
DS3_S: RN4.1 (R1.1), U4.A10 (PT27A/PCLKT0_1)
DS4: J1.23, RN3.5 (R4.2)
DS4_S: RN3.4 (R4.1), U4.B9 (PT22A)
DS5: J1.27, RN3.6 (R3.2)
DS5_S: RN3.3 (R3.1), U4.A9 (PT24A/GR_PCLK0_1)
DS6: J1.28, RN3.7 (R2.2)
DS6_S: RN3.2 (R2.1), U4.A8 (PT18B)
DS7: J1.31, RN3.8 (R1.2)
DS7_S: RN3.1 (R1.1), U4.A7 (PT18A)
DS8: J1.32, RN2.5 (R4.2)
DS8_S: RN2.4 (R4.1), U4.A6 (PT4A)
DS9: J1.33, RN2.6 (R3.2)
DS9_S: RN2.3 (R3.1), U4.B5 (PL2C)
DS10: J1.34, RN2.7 (R2.2)
DS10_S: RN2.2 (R2.1), U4.A5 (PL2B)
DS11: J1.35, RN2.8 (R1.2)
DS11_S: RN2.1 (R1.1), U4.A4 (PL2A)
DS12: J1.36, RN1.5 (R4.2)
DS12_S: RN1.4 (R4.1), U4.B3 (PL5D)
DS13: J1.37, RN1.6 (R3.2)
DS13_S: RN1.3 (R3.1), U4.B2 (PL14C/VREF1_7)
DS14: J1.38, RN1.7 (R2.2)
DS14_S: RN1.2 (R2.1), U4.A2 (PL14A)
DS15: J1.39, RN1.8 (R1.2)
DS15_S: RN1.1 (R1.1), U4.B1 (PL14B)
DS_APD_ADJ: R29.2, U11.4 (IO0)
DS_APD_CAP: C91.1, U9.9 (CAP)
DS_APD_FB: R27.2, R28.1, R29.1, U9.12 (FB)
DS_APD_ISHORT: R30.1, U9.11 (ISHORT)
DS_APD_MON: C93.1, R32.1, U9.4 (MON1), U11.6 (IO2)
DS_APD_MON2: C94.1, R33.1, U9.3 (MON2)
DS_DIN_N: C73.2, R18.1, U6.4 (/DIN)
DS_DIN_P: C72.2, R17.1, U6.1 (DIN)
DS_HV_APD: C90.1, U5.R1 (VAPD), U9.5 (APD)
DS_HV_FILT: C89.1, R25.2, R26.1
DS_HV_MONIN: R26.2, U9.6 (MONIN)
DS_HV_OUT: C88.1, D1.1 (K), R25.1, R27.1
DS_HV_SW: D1.2 (A), L3.2, U9.8 (SW)
DS_LA_N: C76.1, U6.9 (/DOUT)
DS_LA_P: C75.1, U6.12 (DOUT)
DS_RX_N: C76.2, U4.Y6 (HDRXN0_D0CH0)
DS_RX_P: C75.2, U4.Y5 (HDRXP0_D0CH0)
DS_SD: R20.1, U4.U17 (PR47B), U6.7 (SD/LOS), U6.15 (JAM)
DS_SDLVL: R19.1, U6.14 (LOS/SDLVL)
DS_TIA_N: C73.1, U5.R4 (OUT-)
DS_TIA_P: C72.1, U5.R3 (OUT+)
DS_VREF: C74.1, R17.2, R18.2, U6.2 (VREF)
FB_1V1: R1.2, R2.1, U1.5 (FB)
FB_1V1_SD: R3.2, R4.1, U2.5 (FB)
FWD_CLK: J1.1, RN7.8 (R1.2)
FWD_CLK_S: RN7.1 (R1.1), U4.B19 (PT65B)
GND: C1.2, C2.2, C3.2, C4.2, C5.2, C6.2, C7.2, C8.2, C9.2, C10.2, C11.2, C12.2, C13.2, C14.2, C15.2, C16.2, C17.2, C18.2, C19.2, C20.2, C21.2, C22.2, C23.2, C24.2, C25.2, C26.2, C27.2, C28.2, C29.2, C30.2, C31.2, C32.2, C33.2, C34.2, C35.2, C36.2, C37.2, C38.2, C39.2, C40.2, C41.2, C42.2, C43.2, C44.2, C45.2, C46.2, C47.2, C48.2, C49.2, C50.2, C51.2, C52.2, C53.2, C54.2, C55.2, C56.2, C57.2, C58.2, C59.2, C60.2, C61.2, C62.2, C63.2, C64.2, C65.2, C66.2, C67.2, C68.2, C69.2, C70.2, C71.2, C74.2, C77.2, C78.2, C79.2, C80.2, C83.2, C86.2, C87.2, C88.2, C89.2, C90.2, C91.2, C92.2, C93.2, C94.2, C95.2, C96.2, C97.2, C98.2, C99.2, C100.2, C101.2, C102.2, C103.2, C104.2, C105.2, J1.12, J1.30, J2.6, R2.2, R4.2, R14.2, R28.2, R30.2, R32.2, R33.2, R37.2, R39.2, R41.2, R42.2, U1.2 (GND), U2.2 (GND), U3.2 (GND), U4.B7 (GND), U4.B14 (GND), U4.C19 (GND)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
HOLDN: R10.1, U4.R2 (PB15A/HOLDN/DI/BUSY/CSSPIN/CEN)
INITN: R7.1, U4.V3 (INITN)
MISO: J1.19, R46.1, U4.V2 (PB11A/D1/MISO/IO1)
MOSI: J1.17, U4.W2 (PB11B/D0/MOSI/IO0)
PROGRAMN: J1.20, R6.1, U4.W3 (PROGRAMN)
REFCLK_N: U4.Y12 (REFCLKN_D0), Y1.5 (OUT-)
REFCLK_P: U4.Y11 (REFCLKP_D0), Y1.4 (OUT+)
SCL: J1.21, R44.1, U11.16 (SCL)
SDA: J1.22, R45.1, U11.15 (SDA)
SN: J1.40, R9.1, U4.T2 (PB13A/SN/CSN)
SW_1V1: L1.1, U1.3 (SW)
SW_1V1_SD: L2.1, U2.3 (SW)
TCK: J2.2, R14.1, U4.T5 (TCK)
TDI: J2.3, R12.1, U4.R5 (TDI)
TDO: J2.4, U4.V4 (TDO)
TMS: J2.5, R13.1, U4.U5 (TMS)
US0: J1.2, RN6.5 (R4.2)
US0_S: RN6.4 (R4.1), U4.A19 (PT67A)
US1: J1.4, RN6.6 (R3.2)
US1_S: RN6.3 (R3.1), U4.A18 (PT65A)
US2: J1.5, RN6.7 (R2.2)
US2_S: RN6.2 (R2.1), U4.B17 (PT60A)
US3: J1.6, RN6.8 (R1.2)
US3_S: RN6.1 (R1.1), U4.A17 (PT62A)
US4: J1.7, RN5.5 (R4.2)
US4_S: RN5.4 (R4.1), U4.A16 (PT56A)
US5: J1.8, RN5.6 (R3.2)
US5_S: RN5.3 (R3.1), U4.B15 (PT51A)
US6: J1.9, RN5.7 (R2.2)
US6_S: RN5.2 (R2.1), U4.B13 (PT42A)
US7: J1.10, RN5.8 (R1.2)
US7_S: RN5.1 (R1.1), U4.A13 (PT40B)
US_APD_ADJ: R38.2, U11.5 (IO1)
US_APD_CAP: C100.1, U10.9 (CAP)
US_APD_FB: R36.2, R37.1, R38.1, U10.12 (FB)
US_APD_ISHORT: R39.1, U10.11 (ISHORT)
US_APD_MON: C102.1, R41.1, U10.4 (MON1), U11.7 (IO3)
US_APD_MON2: C103.1, R42.1, U10.3 (MON2)
US_DIN_N: C82.2, R22.1, U8.4 (/DIN)
US_DIN_P: C81.2, R21.1, U8.1 (DIN)
US_HV_APD: C99.1, U7.2 (VAPD), U10.5 (APD)
US_HV_FILT: C98.1, R34.2, R35.1
US_HV_MONIN: R35.2, U10.6 (MONIN)
US_HV_OUT: C97.1, D2.1 (K), R34.1, R36.1
US_HV_SW: D2.2 (A), L4.2, U10.8 (SW)
US_LA_N: C85.1, U8.9 (/DOUT)
US_LA_P: C84.1, U8.12 (DOUT)
US_RX_N: C85.2, U4.Y8 (HDRXN0_D0CH1)
US_RX_P: C84.2, U4.Y7 (HDRXP0_D0CH1)
US_SD: R24.1, U4.T17 (PR47D/LRC_GPLL0C_IN), U8.7 (SD/LOS), U8.15 (JAM)
US_SDLVL: R23.1, U8.14 (LOS/SDLVL)
US_TIA_N: C82.1, U7.3 (OUT-)
US_TIA_P: C81.1, U7.5 (OUT+)
US_VREF: C83.1, R21.2, R22.2, U8.2 (VREF)
VCXO_PWM: R15.1, U4.U16 (PR47C/LRC_GPLL0T_IN)
VCXO_RC: C66.1, R15.2, R16.1
VCXO_VC: C67.1, R16.2, Y1.1 (VIN)

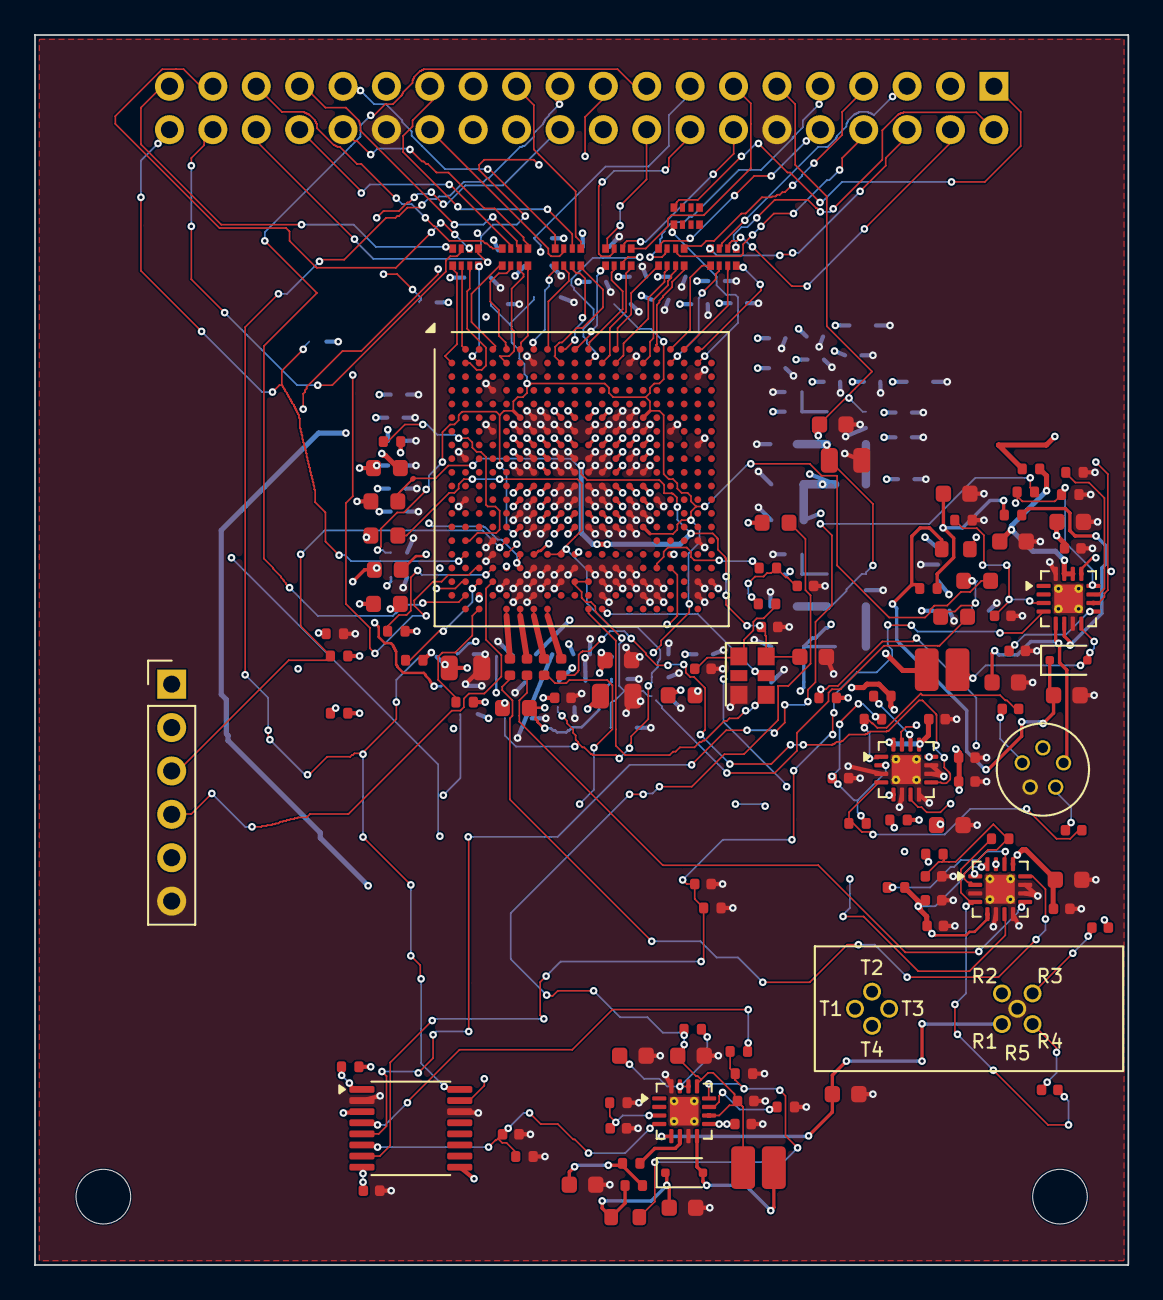
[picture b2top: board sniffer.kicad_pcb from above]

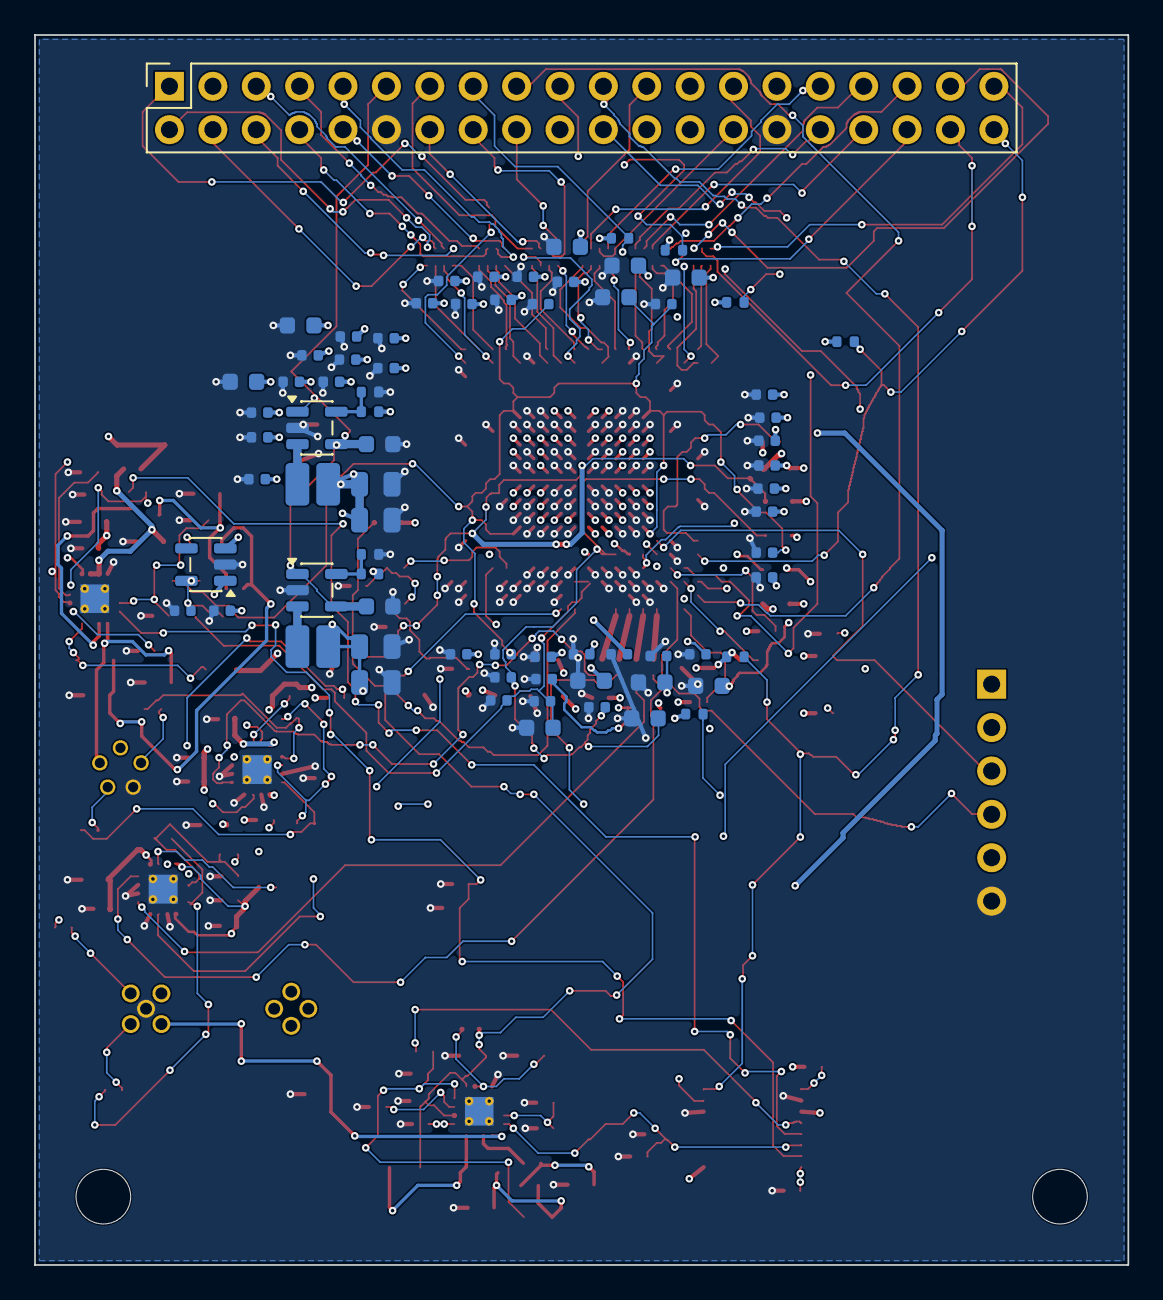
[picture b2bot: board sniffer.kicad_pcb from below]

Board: 4 copper layers, 64.0 x 72.0 mm, 190 parts (74 on the bottom side), 138 nets.
